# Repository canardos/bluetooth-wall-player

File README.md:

# Bluetooth Wall Audio Player

## A low power, wall mounted, Bluetooth audio player, clock, and environmental monitor

> [!Warning]
> This is personal project. It was built and works without issue for my purposes. It is made public here in case some part of it is useful to others, but **neither the hardware nor firmware have been rigorously tested**.

**Features:**

- Media/volume controls
- Song metadata display
- Time, temperature, pressure, humidity display on idle
- Ultra low power sleep with proximity sensing wakeup
- Differential analog and S/PDIF digital audio output

**This repo contains the firmware and PCB/enclosure design.**

**See [custom electronics projects at duk.io](https://www.duk.io/blog/electronics-projects/) for full project details.**

## Build

The project uses the [PlatformIO](https://platformio.org/) dependency management/build system. If you have PlatformIO installed, executing the `run` command in the root folder *should* 🙏 be all that is required for a successful build. The `platformio.ini` file contains the required configuration  and PlatformIO will download the required platform dependencies and toolchain.

**1. Clone repo and download submodules**

```shell
> git clone https://github.com/canardos/bluetooth-wall-player.git
> cd bluetooth-wall-player
> git submodule update --init
```

**2. Build firmware (PlatformIO must be installed)**

```shell
> pio run

```

**3. Upload to device**

Similarly, use `pio run --target upload` to upload the firmware to the device. You'll likely need to update the upload settings in `platformio.ini` to reflect your settings, or use your own upload tool.

```shell
> pio run --target upload

```

**4. [optional] Create project files for IDE**

If you want to view/edit the project in your favorite IDE, use PlatformIO to generate the appropriate setup/workspace files and import the project:

```shell
> pio project init --ide [atom|clion|codeblocks|eclipse|emacs|netbeans|qtcreator|sublimetext|vim|visualstudio|vscode]
```

See the [PlatformIO documentation](https://docs.platformio.org) for further details.

#### Using an alternate build system

**Platform dependencies**

If you wish to use a different build system, you will need:

| | |
|-|-|
| ST STM32 CMSIS headers | Peripheral/register definitions |
| CMSIS headers/source | CMSIS HAL functionality - SysTick_Config, NVIC_xxx etc.|
| CMSIS Cortex-M3 system source | `SystemInit()`/`SystemCoreClockUpdate()` implementation and `SystemCoreClock`|
| Startup source file | ASM file containing the startup code and vector table |
| Linker script | Tells the linker how to setup everything in flash/SRAM |

All of these are available in the [STM32 SDK](https://www.st.com/en/development-tools/stm32-software-development-tools.html) available from ST Micro.

**Compiling / linking**

`platformio.ini` lists the required compiler flags. Be sure to use `--specs=nano.specs` and `--specs=nosys.specs` when linking using your own tools.

#### Compiler

The project was built with `gcc-arm-none-eabi 9.2.1` It should work with any later GCC version and possibly with other compilers. The code contains some GCC flags and some C99 VLAs.

#### Target requirements

| | |
|-|-|
|MCU  | STM32F1xx |
|Flash| >42kb     |
|SRAM | >8kb      |

## Dependencies (firmware)

**CMSIS**

PlatformIO should automatically include/link the correct headers/sources from the STM32 SDK. Version 9.0.0 was used in production.

**Libpekin**

[Libpekin](https://github.com/canardos/libpekin) is a collection of shared MCU-related code resulting from this and other projects. It's included as a Git submodule in the `lib` folder. PlatformIO will include the `lib` subfolders automatically.

## Hardware

#### PCB

The PCB was designed with KiCad v.5, but the files have been upgraded to v.7 and are located in `/hardware/pcb`. Gerber output for the first revision is located in `/hardware/pcb/plots_rev_a`.

> [!Important]
> [Several fixes have been made to the design](https://www.duk.io/blog/electronics-projects/bt-player/bluetooth-audio-player-conclusion/#problems-and-screwups), which are implemented in the latest schematic/pcb files, but are not present in the revision A plot output.

See the [KiCad documentation](https://docs.kicad.org/) for information on installing and using KiCad.

**Custom symbols and footprints required by the board are included as a Git submodule at `/hardware/pcb/kicad-mycustom-lib`, and are included in the KiCad project as a project-specific library.**

#### Enclosure

The [enclosure design](http://www.duk.io/blog/electronics-projects/bt-player/bluetooth-audio-player-mechanical-design/#mechanical-design) includes a [laser-cut wooden facade](http://www.duk.io/blog/electronics-projects/bt-player/bluetooth-audio-player-mechanical-design/#laser-etched-wood-facade). The CAD files for the design are located in `/hardware/enclosure/laser_cut_facade`.

A Sketchup model I used to model the mechanical constraints of the design is included in `/hardware/enclosure`.

## Folder structure

```
BTWallPlayer
|
+--artwork           | SVG sources for animation
|  |
|  +--render         | bitmap output frames
|
+--hardware
|  |
|  +--pcb           | KiCad schematic and board design files
|  +--enclosure     | Enclosure Sketchup model and laser cutting
|                   | design files
|
+--lib
|  |
|  +--libpekin       | Libpekin platform independent code
|  +--libpekin_stm32 | Libpekin STM32 specific code
|
+--src
|  |
|  +--data           | Image and font data
|  +--devices        | Hardware device drivers
|
|--test              | No tests in use

```

## License

This software is available under the [MIT license](https://opensource.org/license/MIT).

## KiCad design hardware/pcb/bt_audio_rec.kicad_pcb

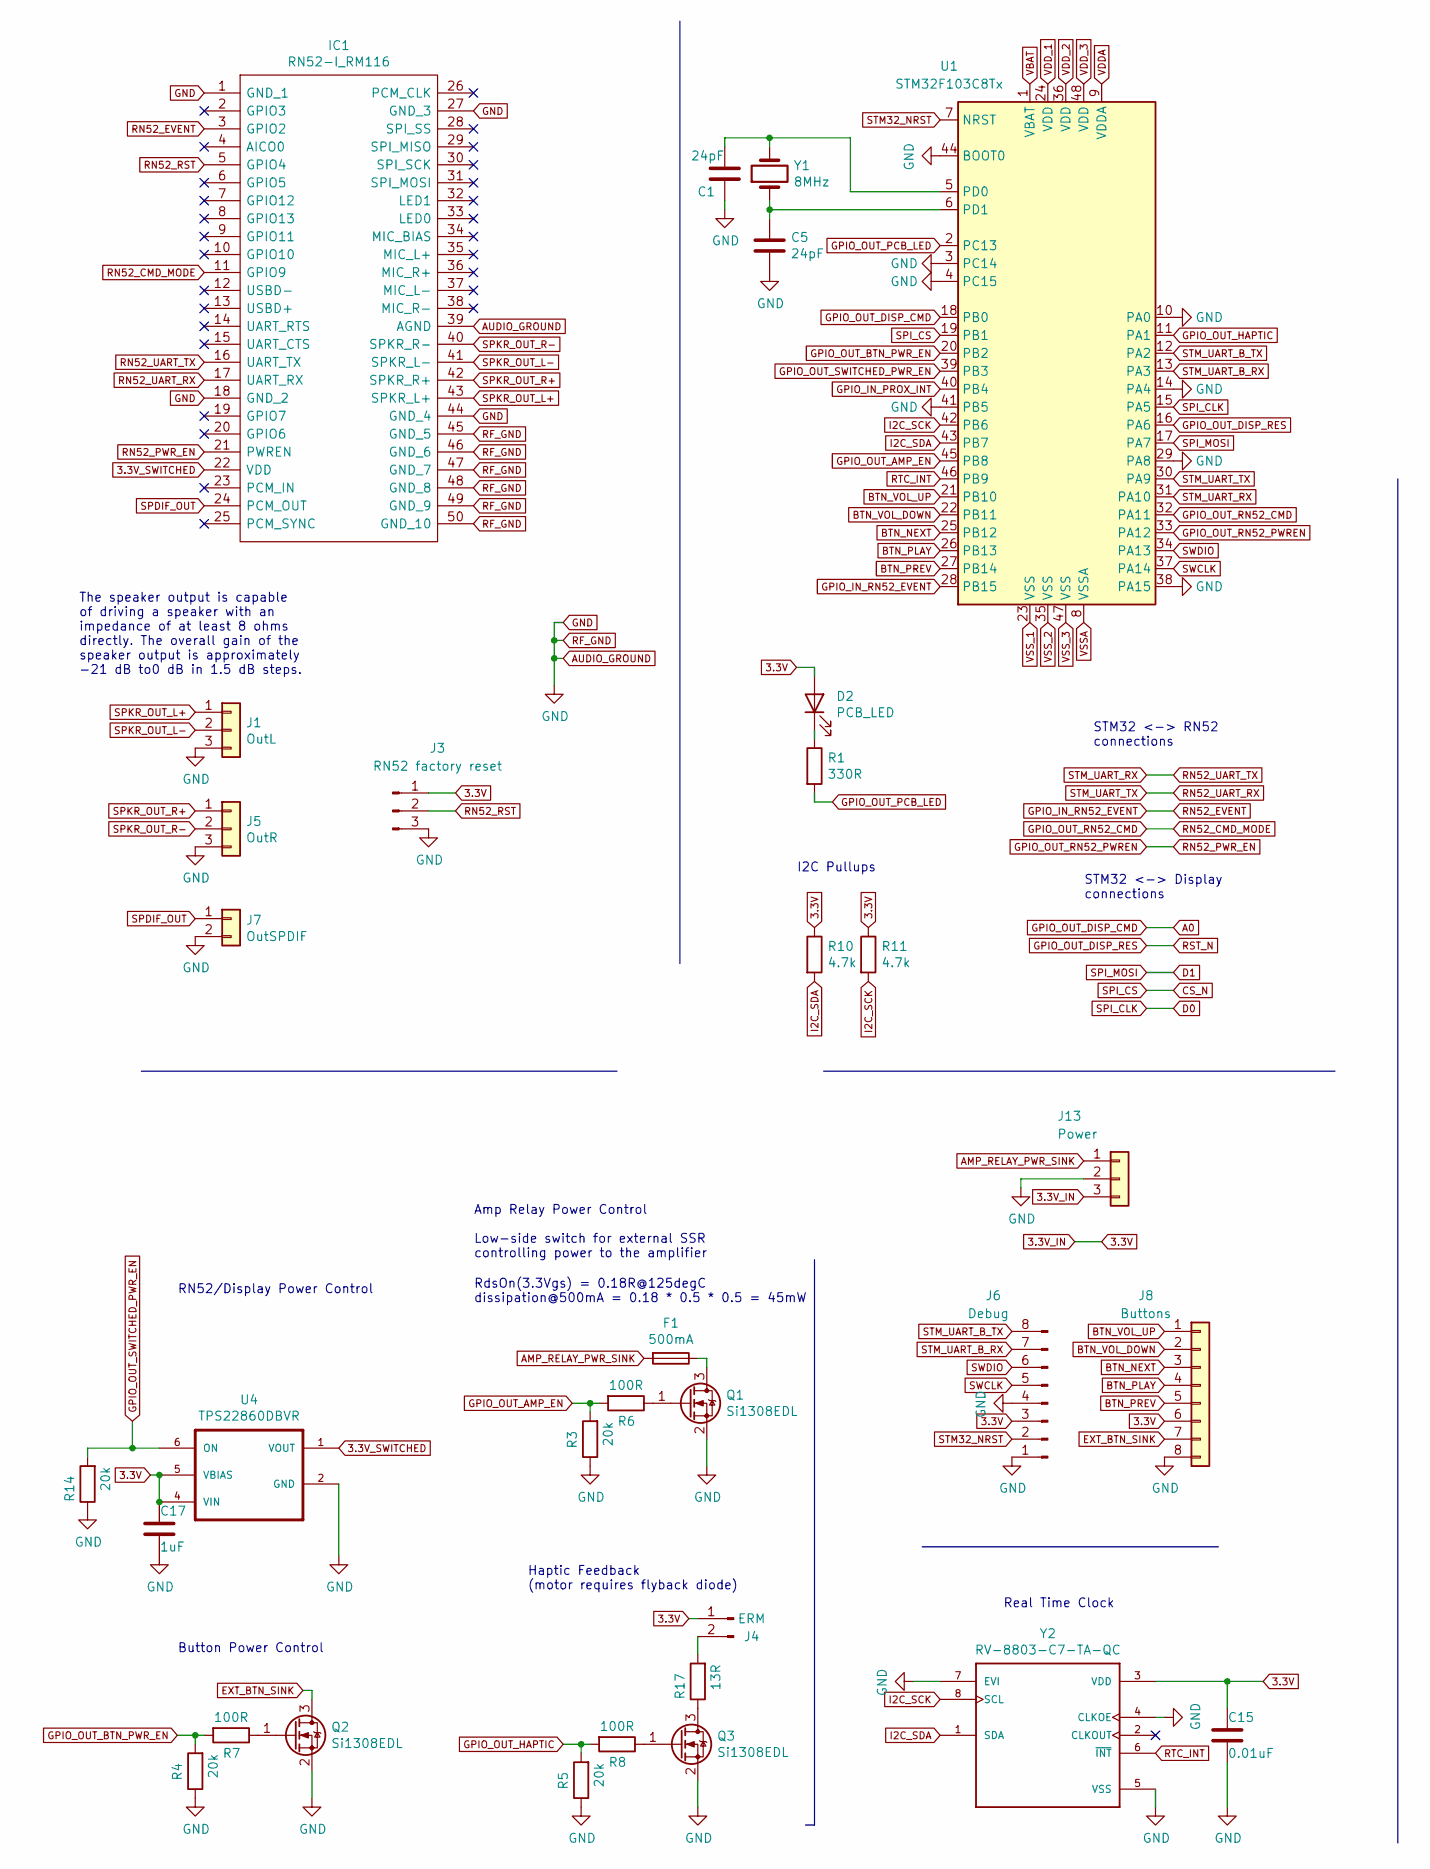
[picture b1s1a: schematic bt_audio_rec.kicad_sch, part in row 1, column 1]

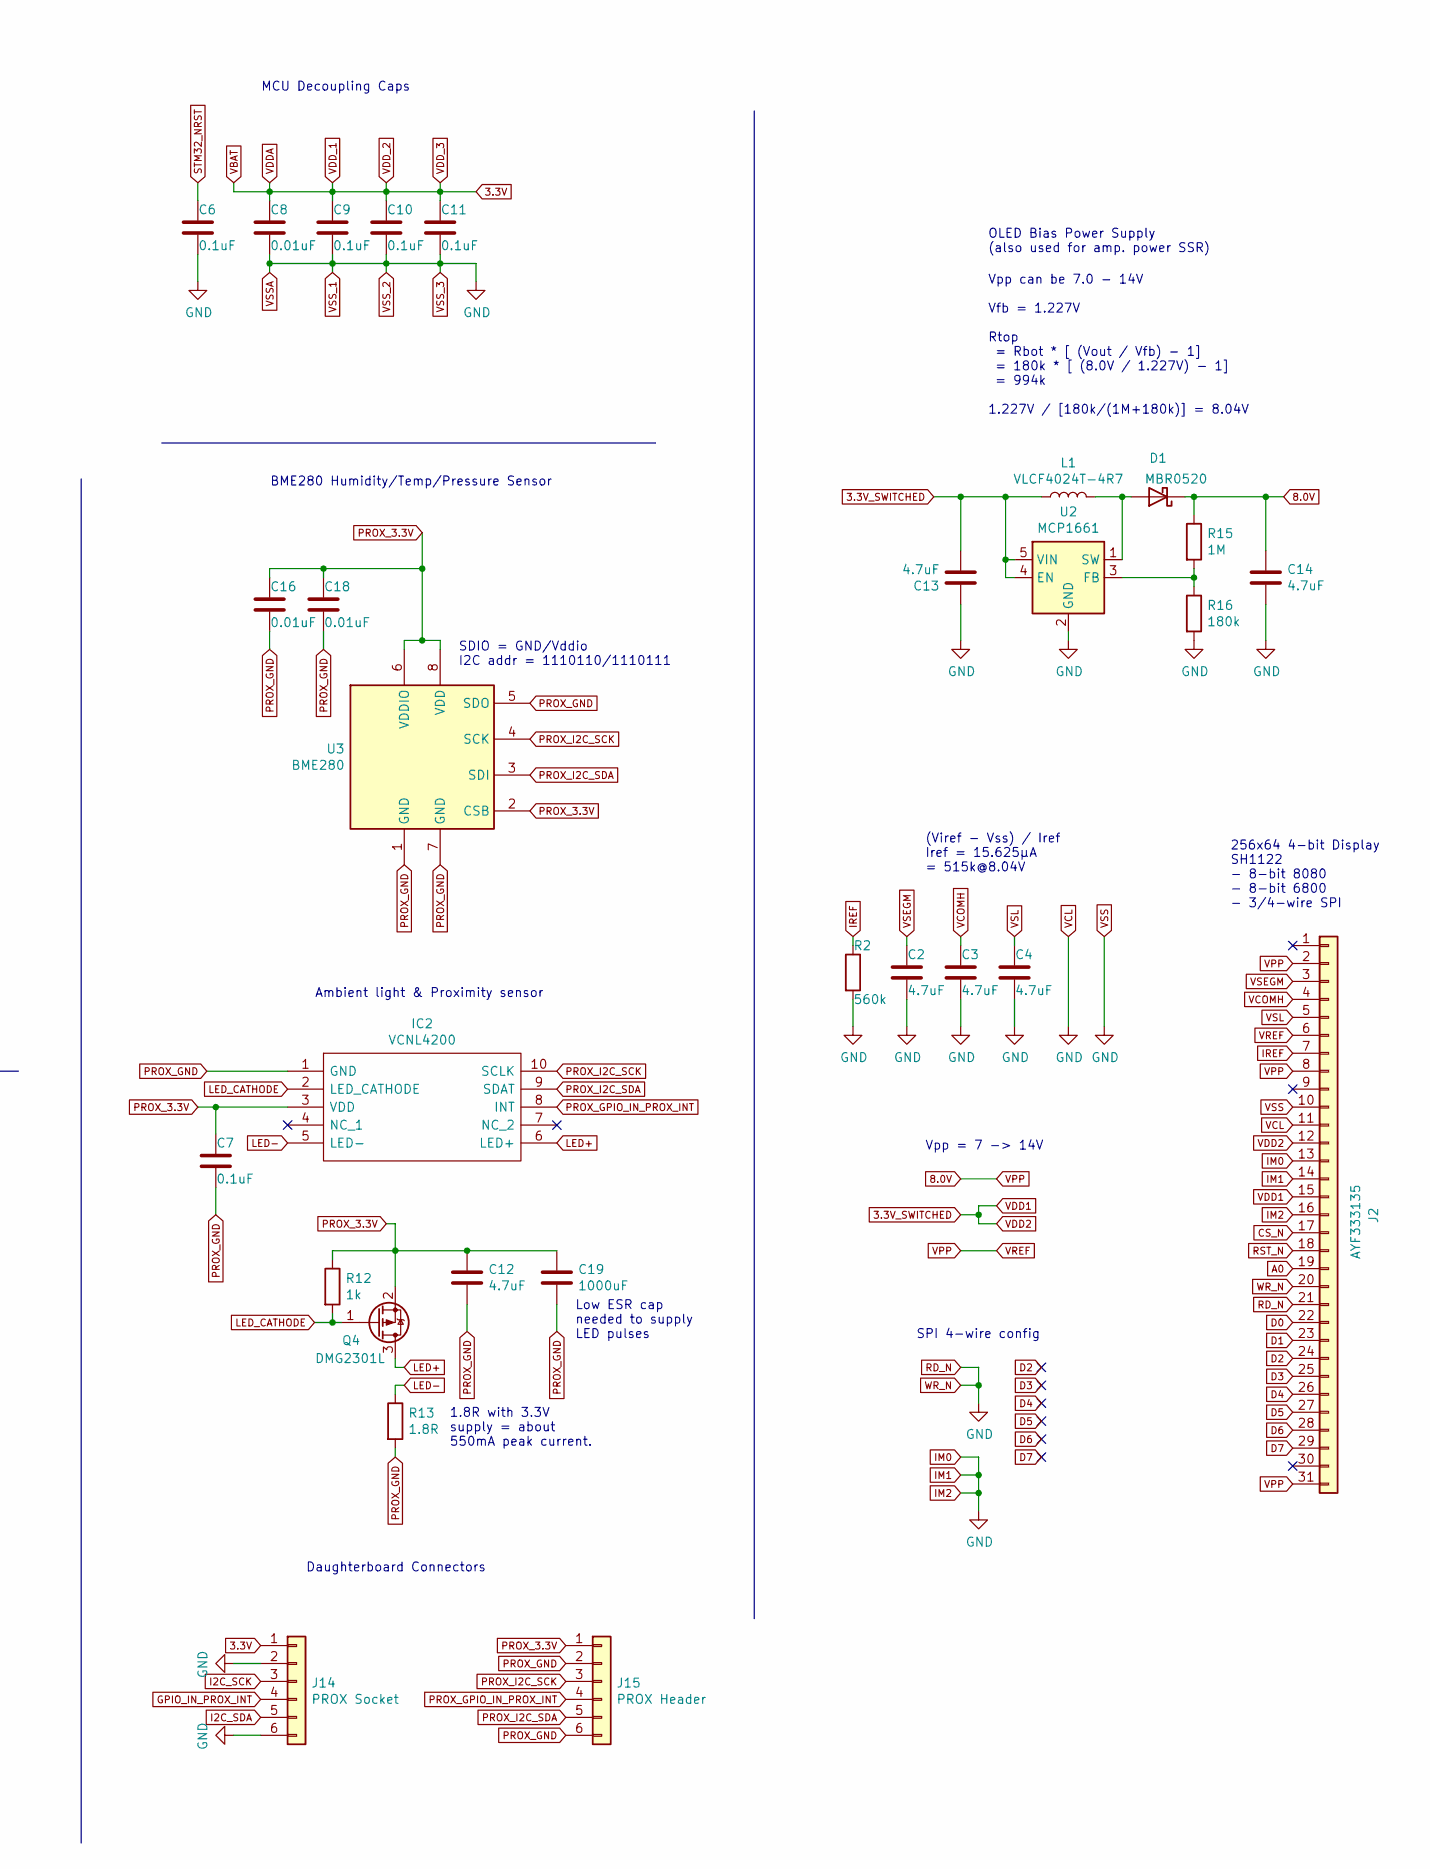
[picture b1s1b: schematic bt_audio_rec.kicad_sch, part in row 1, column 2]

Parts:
C1, C5: 24pF; C_0402_1005Metric
C2, C3, C4, C12, C13, C14: 4.7uF; C_0603_1608Metric
C6, C7, C9, C10, C11: 0.1uF; C_0402_1005Metric
C8, C15, C16, C18: 0.01uF; C_0402_1005Metric
C17: 1uF; C_0805_2012Metric
C19: 1000uF; C_Radial_D6.3mm_H7.0mm_P2.50mm
D1: MBR0520; D_SOD-123
D2: PCB_LED; D_0603_1608Metric
F1: 500mA; R_Axial_DIN0207_L6.3mm_D2.5mm_P10.16mm_Horizontal
IC1: RN52-I_RM116; Bluetooth_module_Microchip_RN52; Manufacturer_Part_Number RN52-I/RM116; Mouser Part Number 579-RN52-I/RM116
IC2: VCNL4200; Proximity_Sensor_Vishay_VCNL4200; Manufacturer_Part_Number VCNL4200; Mouser Part Number 78-VCNL4200
J1: OutL; JST_PH_B3B-PH-K_1x03_P2.00mm_Vertical
J2: AYF333135; FPC_Socket_0.3_31_Panasonic_AYF333135
J3: RN52 factory reset; PinHeader_1x03_P2.54mm_Horizontal
J4: ERM; PinHeader_1x02_P2.54mm_Horizontal
J5: OutR; JST_PH_B3B-PH-K_1x03_P2.00mm_Vertical
J6: Debug; PinSocket_2x04_P2.54mm_Vertical
J7: OutSPDIF; JST_PH_B2B-PH-K_1x02_P2.00mm_Vertical
J8: Buttons; PinHeader_1x08_P2.54mm_Horizontal
J13: Power; Molex_KK-254_AE-6410-03A_1x03_P2.54mm_Vertical
J14: PROX Socket; PinSocket_2x03_P2.54mm_Vertical
J15: PROX Header; PinHeader_2x03_P2.54mm_Vertical
L1: VLCF4024T-4R7; Inductor_L_TDK_VLCF4024
Q1, Q2, Q3: Si1308EDL; SOT-323_SC-70
Q4: DMG2301L; SOT-23
R1: 330R; R_0603_1608Metric
R2: 560k; R_0603_1608Metric
R3, R4, R5, R14: 20k; R_0603_1608Metric
R6, R7, R8: 100R; R_0603_1608Metric
R10, R11: 4.7k; R_0603_1608Metric
R12: 1k; R_0603_1608Metric
R13: 1.8R; R_0603_1608Metric
R15: 1M; R_0603_1608Metric
R16: 180k; R_0603_1608Metric
R17: 13R; R_0603_1608Metric
U1: STM32F103C8Tx; LQFP-48_7x7mm_P0.5mm
U2: MCP1661; SOT-23-5
U3: BME280; Bosch_LGA-8_2.5x2.5mm_P0.65mm_ClockwisePinNumbering
U4: TPS22860DBVR; SOT-23-6
Y1: 8MHz; Crystal_SMD_HC49-SD
Y2: RV-8803-C7-TA-QC; RTC_Microcrystal_RV-8803-C7-TA-QC

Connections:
3.3V: C8.1, C9.1, C10.1, C11.1, C15.1, C17.1, D2.2 (A), J3.1, J4.1, J6.3, J8.6, J13.3, J14.1, R10.1, R11.1, U1.1 (VBAT), U1.9 (VDDA), U1.24 (VDD), U1.36 (VDD), U1.48 (VDD), U4.4 (VIN), U4.5 (VBIAS), Y2.3 (VDD)
3.3V_SWITCHED: C13.2, IC1.22 (VDD), J2.12, J2.15, L1.1, U2.4 (EN), U2.5 (VIN), U4.1 (VOUT)
8.0V: C14.1, D1.1 (K), J2.2, J2.6, J2.8, J2.31, R15.1
A0: J2.19, U1.18 (PB0)
AMP_RELAY_PWR_SINK: F1.2, J13.1
AUDIO_GROUND: C1.1, C2.2, C3.2, C4.2, C5.2, C6.2, C8.2, C9.2, C10.2, C11.2, C13.1, C14.2, C15.2, C17.2, IC1.1 (GND_1), IC1.18 (GND_2), IC1.27 (GND_3), IC1.39 (AGND), IC1.44 (GND_4), IC1.45 (GND_5), IC1.46 (GND_6), IC1.47 (GND_7), IC1.48 (GND_8), IC1.49 (GND_9), IC1.50 (GND_10), J1.3, J2.10, J2.11, J2.13, J2.14, J2.16, J2.20, J2.21, J3.3, J5.3, J6.1, J6.4, J7.2, J8.8, J13.2, J14.2, J14.6, Q1.2 (S), Q2.2 (S), Q3.2 (S), R2.2, R3.1, R4.1, R5.1, R14.1, R16.2, U1.3 (PC14), U1.4 (PC15), U1.8 (VSSA), U1.10 (PA0), U1.14 (PA4), U1.23 (VSS), U1.29 (PA8), U1.35 (VSS), U1.38 (PA15), U1.41 (PB5), U1.44 (BOOT0), U1.47 (VSS), U2.2 (GND), U4.2 (GND), Y2.4 (CLKOE), Y2.5 (VSS), Y2.7 (EVI)
BTN_NEXT: J8.3, U1.25 (PB12)
BTN_PLAY: J8.4, U1.26 (PB13)
BTN_PREV: J8.5, U1.27 (PB14)
BTN_VOL_DOWN: J8.2, U1.22 (PB11)
BTN_VOL_UP: J8.1, U1.21 (PB10)
CS_N: J2.17, U1.19 (PB1)
D0: J2.22, U1.15 (PA5)
D1: J2.23, U1.17 (PA7)
D2: J2.24
D3: J2.25
D4: J2.26
D5: J2.27
D6: J2.28
D7: J2.29
EXT_BTN_SINK: J8.7, Q2.3 (D)
GPIO_IN_PROX_INT: J14.4, U1.40 (PB4)
GPIO_IN_RN52_EVENT: IC1.3 (GPIO2), U1.28 (PB15)
GPIO_OUT_AMP_EN: R3.2, R6.2, U1.45 (PB8)
GPIO_OUT_BTN_PWR_EN: R4.2, R7.2, U1.20 (PB2)
GPIO_OUT_DISP_RES: J2.18, U1.16 (PA6)
GPIO_OUT_HAPTIC: R5.2, R8.2, U1.11 (PA1)
GPIO_OUT_PCB_LED: R1.2, U1.2 (PC13)
GPIO_OUT_RN52_CMD: IC1.11 (GPIO9), U1.32 (PA11)
GPIO_OUT_RN52_PWREN: IC1.21 (PWREN), U1.33 (PA12)
GPIO_OUT_SWITCHED_PWR_EN: R14.2, U1.39 (PB3), U4.6 (ON)
I2C_SCK: J14.3, R11.2, U1.42 (PB6), Y2.8 (SCL)
I2C_SDA: J14.5, R10.2, U1.43 (PB7), Y2.1 (SDA)
IREF: J2.7, R2.1
LED+: IC2.6 (LED+), Q4.3 (D)
LED-: IC2.5 (LED-), R13.1
LED_CATHODE: IC2.2 (LED_CATHODE), Q4.1 (G), R12.2
unnamed: C1.2, U1.5 (PD0), Y1.2
unnamed: C5.1, U1.6 (PD1), Y1.1
unnamed: D1.2 (A), L1.2, U2.1 (SW)
unnamed: D2.1 (K), R1.1
unnamed: F1.1, Q1.3 (D)
unnamed: J4.2, R17.2
unnamed: Q1.1 (G), R6.1
unnamed: Q2.1 (G), R7.1
unnamed: Q3.1 (G), R8.1
unnamed: Q3.3 (D), R17.1
unnamed: R15.2, R16.1, U2.3 (FB)
PROX_3.3V: C7.1, C12.1, C16.1, C18.1, C19.1, IC2.3 (VDD), J15.1, Q4.2 (S), R12.1, U3.2 (CSB), U3.6 (VDDIO), U3.8 (VDD)
PROX_GND: C7.2, C12.2, C16.2, C18.2, C19.2, IC2.1 (GND), J15.2, J15.6, R13.2, U3.1 (GND), U3.5 (SDO), U3.7 (GND)
PROX_GPIO_IN_PROX_INT: IC2.8 (INT), J15.4
PROX_I2C_SCK: IC2.10 (SCLK), J15.3, U3.4 (SCK)
PROX_I2C_SDA: IC2.9 (SDAT), J15.5, U3.3 (SDI)
RN52_RST: IC1.5 (GPIO4), J3.2
RN52_UART_RX: IC1.17 (UART_RX), U1.30 (PA9)
RN52_UART_TX: IC1.16 (UART_TX), U1.31 (PA10)
RTC_INT: U1.46 (PB9), Y2.6 (~INT)
SPDIF_OUT: IC1.24 (PCM_OUT), J7.1
SPKR_OUT_L+: IC1.43 (SPKR_L+), J1.1
SPKR_OUT_L-: IC1.41 (SPKR_L-), J1.2
SPKR_OUT_R+: IC1.42 (SPKR_R+), J5.1
SPKR_OUT_R-: IC1.40 (SPKR_R-), J5.2
STM32_NRST: C6.1, J6.2, U1.7 (NRST)
STM_UART_B_RX: J6.7, U1.13 (PA3)
STM_UART_B_TX: J6.8, U1.12 (PA2)
SWCLK: J6.5, U1.37 (PA14)
SWDIO: J6.6, U1.34 (PA13)
VCOMH: C3.1, J2.4
VSEGM: C2.1, J2.3
VSL: C4.1, J2.5

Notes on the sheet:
Haptic Feedback (motor requires flyback diode)
Daughterboard Connectors
I2C Pullups
Amp Relay Power Control Low-side switch for external SSR controlling power to the amplifier
Vpp can be 7.0 - 14V Vfb = 1.227V Rtop = Rbot * [ (Vout / Vfb) - 1] = 180k * [ (8.0V / 1.227V) - 1] = 994k 1.227V / [180k/(1M+180k)] = 8.04V
BME280 Humidity/Temp/Pressure Sensor
SDIO = GND/Vddio I2C addr = 1110110/1110111
(Viref - Vss) / Iref Iref = 15.625μA = 515k@8.04V
The speaker output is capable of driving a speaker with an impedance of at least 8 ohms directly. The overall gain of the speaker output is approximately -21 dB to0 dB in 1.5 dB steps.
Low ESR cap needed to supply LED pulses
Button Power Control
RdsOn(3.3Vgs) = 0.18R@125degC dissipation@500mA = 0.18 * 0.5 * 0.5 = 45mW
1.8R with 3.3V supply = about 550mA peak current.
Vpp = 7 -> 14V
STM32 <-> Display connections
Ambient light & Proximity sensor
RN52/Display Power Control
OLED Bias Power Supply (also used for amp. power SSR)
Real Time Clock
STM32 <-> RN52 connections
256x64 4-bit Display SH1122 - 8-bit 8080 - 8-bit 6800 - 3/4-wire SPI
MCU Decoupling Caps
SPI 4-wire config

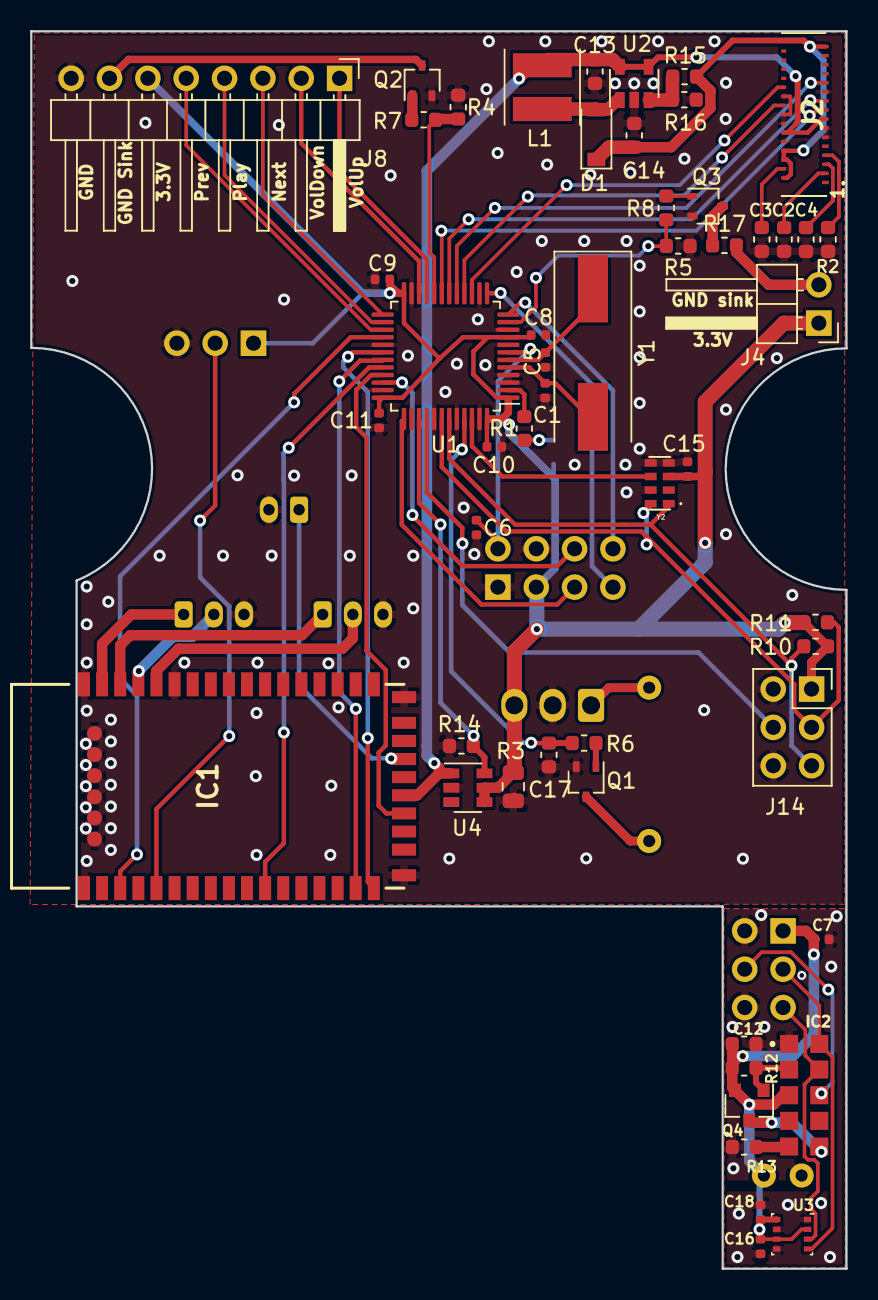
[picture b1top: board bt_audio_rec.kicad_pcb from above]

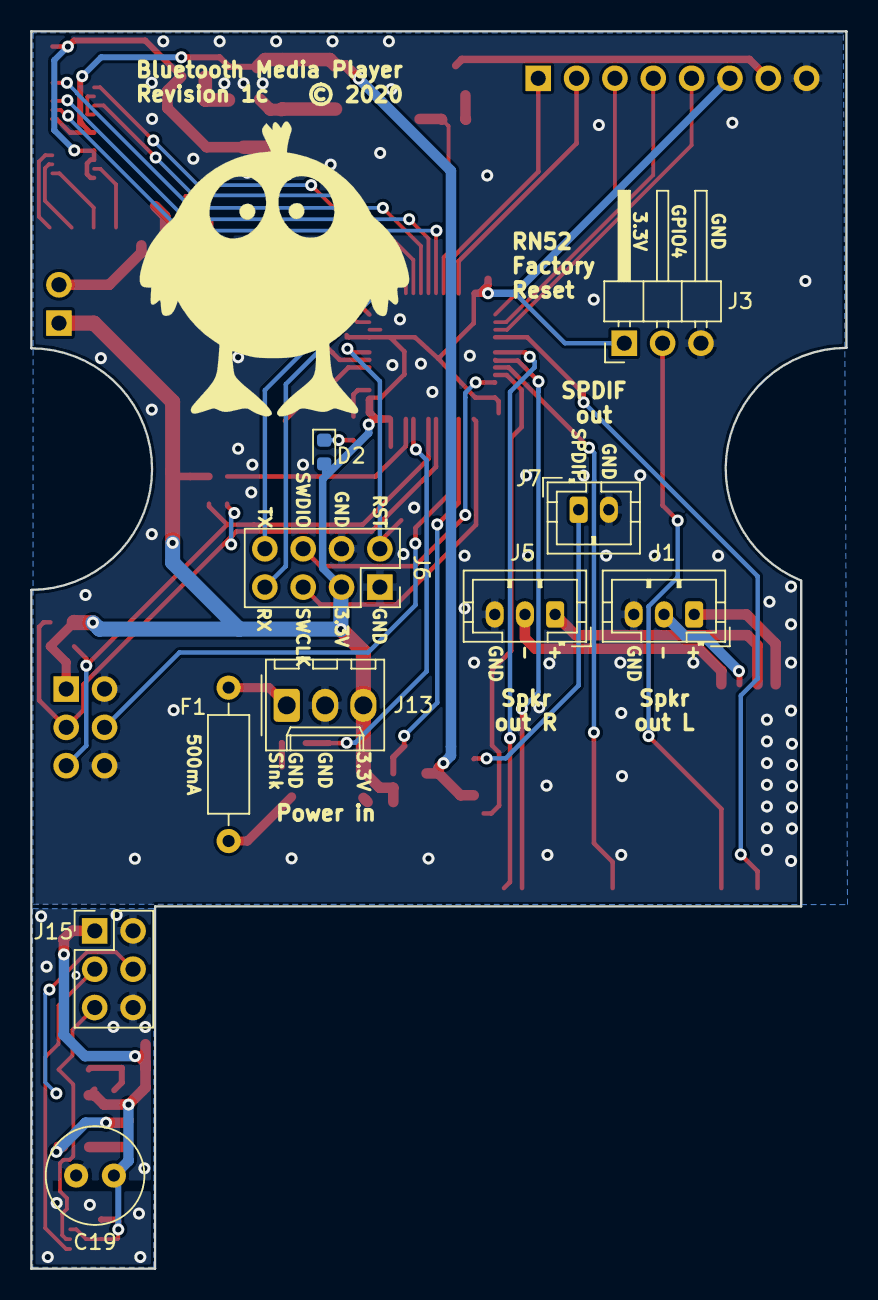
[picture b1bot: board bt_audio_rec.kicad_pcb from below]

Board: 2 copper layers, 54.0 x 82.0 mm, 62 parts (10 on the bottom side), 64 nets.

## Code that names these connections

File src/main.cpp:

#include "libpekin.h"
#include "string_util.h"
#include "libpekin_stm32_hal.h"
#include "clock_stm32f1xx.h"

#include <bt_module.h>
#include <error_handler.h>
#include <event_queue.h>
#include <player_state_machine.h>

#include <devices/peripherals.h>
#include <devices/rn52.h>
#include "devices/oled.h"
#include "devices/sensors.h"
#include "devices/rtc.h"

/*
3.3V / GND / sink
blue /white/brown, left to right front of faceplate
brown/black/blue cable
*/

using namespace Libp;
using namespace LibpStm32;

static BtModule bt_module_(getRn52());
static Display display(getOled());
static PwrControl pwr_ctrl;
static EventQueue queue_;
static PlayerStateMachine player(queue_, bt_module_, display, pwr_ctrl);

void initSysClock()
{
    Clk::setSysClk(Clk::SysClkSrc::ext_high_speed_osc, 2, Clk::PllSrc::hse, 2);
    // 24 MHz
    Clk::setSysClk(Clk::SysClkSrc::pll, 2, Clk::PllSrc::hse, 3);
    // APB1 can't exceed 36 MHz
    Clk::setPeripheralClk(Clk::ApbPrescaler::div1, Clk::ApbPrescaler::div1);
}

void initSensors()
{
    if (!initTempSensor()) {
        getErrHndlr().halt(ErrorCode::module_init_fail, "BME280 init failed");
    }
    if (!initRtc()) {
        getErrHndlr().halt(ErrorCode::module_init_fail, "RTC init failed");
    }

    display.drawText(Display::TextPos::fullscreen, "Calibrating proximity", "in 3");
    delayMs(1000);
    display.drawText(Display::TextPos::fullscreen, "Calibrating proximity", "in 2");
    delayMs(1000);
    display.drawText(Display::TextPos::fullscreen, "Calibrating proximity", "in 1");
    delayMs(1000);

    uint16_t prox_count = initProxSensor();
    if (prox_count == 0) {
        getErrHndlr().halt(ErrorCode::module_init_fail, "Prox init failed");
    }

    constexpr uint8_t max_len = strlen("Done ()") + Libp::maxStrLen<uint16_t>();
    char buf[max_len];
    snprintf(buf, max_len, "Done (%d)", prox_count);
    display.drawText(Display::TextPos::fullscreen, buf, "Initializing Bluetooth...");

    TimeData time_data = {0};
    time_data.year = 20;
    time_data.month = 1;
    time_data.day_of_month = 1;
    setTime(time_data);
}

//#define TEST_PROX_MODE

#ifdef TEST_PROX_MODE
void drawProx()
{
    char buf[50];
    while (true) {
        uint16_t count = getProxCount();
        snprintf(buf, 50, "Count: %d", count);
        display.drawText(Display::TextPos::fullscreen, buf, "");
        delayMs(300);
    }
}
#endif

void initPeripherals()
{
    initGpio();  // enable GPIO clocks before peripherals init
    initSerial();
    initSpi();
    initI2c();
    initTimers();
    initErrHndlr();
}

int main(void)
{
    initSysClock();
    libpekinInitTimers();
    initPeripherals();
    pwr_ctrl.setState(PwrControl::PwrState::clock); // needs errHndlr
    oledInit();                                     // needs SPI and timers
    initSensors();                                  // needs I2C, timers, and display
#ifdef TEST_PROX_MODE
    drawProx();
#endif
    initRn52();
    if (!bt_module_.init()) {
        getErrHndlr().halt(ErrorCode::module_init_fail, "BT init failed");
    }
    enableExtIrqs();
    clearProxInterrupt();
    player.run();
}

#ifdef __cplusplus
extern "C" {
#endif

/// Triggered by RN52 event on GPIO2 and button presses
__attribute__ ((interrupt("IRQ")))
void EXTI15_10_IRQHandler(void)
{
    disableExtIrqs();
    getErrHndlr().report("\r\nEXTI15_10_IRQ\r\n");

    // --- RN52 event ---

    if (Pins::rn52_gpio2.irqIsPending()) {
        queue_.postEvent(EventType::rn52_gpio2);
        Pins::rn52_gpio2.clearPendingIrqBit();
    }

    // --- Button events ---

    if (Pins::btn_play.irqIsPending()) {
        bool pressed = Pins::btn_play.read();
        getErrHndlr().report("Play: %d\r\n", (int)pressed);
        queue_.postEvent(pressed ? EventType::btn_play : EventType::btn_play_release);
        Pins::btn_play.clearPendingIrqBit();
    }
    if (Pins::btn_vol_up.irqIsPending()) {
        queue_.postEvent(EventType::btn_vol_up);
        Pins::btn_vol_up.clearPendingIrqBit();
    }
    if (Pins::btn_vol_dn.irqIsPending()) {
        queue_.postEvent(EventType::btn_vol_dn);
        Pins::btn_vol_dn.clearPendingIrqBit();
    }
    if (Pins::btn_next.irqIsPending()) {
        queue_.postEvent(EventType::btn_next);
        Pins::btn_next.clearPendingIrqBit();
    }
    if (Pins::btn_prev.irqIsPending()) {
        queue_.postEvent(EventType::btn_prev);
        Pins::btn_prev.clearPendingIrqBit();
    }
    Pins::btn_prev.clearPendingIrqLine();
    //__DSB();
    enableExtIrqs();
}

/// Triggered by RTC minute tick
__attribute__ ((interrupt("IRQ")))
void EXTI9_5_IRQHandler(void)
{
    getErrHndlr().report("\r\nEXTI9_5_IRQ\r\n");
    if (Pins::rtc_int.irqIsPending()) {
        queue_.postEvent(EventType::clock_tick);
        Pins::rtc_int.clearPendingIrqBit();
    }
    Pins::rtc_int.clearPendingIrqLine();
    __DSB();
}

/// Triggered by proximity sensor
__attribute__ ((interrupt("IRQ")))
void EXTI4_IRQHandler(void)
{
    getErrHndlr().report("\r\nEXTI4_IRQ\r\n");
    if (Pins::proximity_int.irqIsPending()) {
        queue_.postEvent(EventType::proximity_trigger);
        Pins::proximity_int.clearPendingIrqBit();
    }
    Pins::proximity_int.clearPendingIrqLine();
    __DSB();
}

#ifdef __cplusplus
}
#endif

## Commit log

2020-03-12 Initial commit - PCB hardware production ver.A
2020-09-09 Update proximity cap value, upate PCB notes.
2020-09-22 Fix GPIO4 tied low and backwards MOSFET error
2020-09-23 Update connector label
2020-09-23 Rename plot output folder
2020-09-24 Connect unused pins to ground
2020-09-25 Add duk.io logo
2020-09-26 Change LED resistor
2020-09-29 Add FPC pin number label
2020-10-14 Add decoupling cap to proximity LED
    See https://www.duk.io/blog/electronics-projects/bt-player/bluetooth-audio-player-firmware
2020-11-19 Add flyback label
2024-03-29 Migrate to KiCad 7
    Update schematic/pcb and rescue symbols as required
    Move custom library to a project specific submodule
    Fix missing duk.io logo
    Update gitignore
    Remove old files
2024-04-01 Add project firmware
2024-04-01 Add hardware enclosure files
2024-04-01 Update libpekin library to correct commit

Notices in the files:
hardware/pcb/bt_audio_rec.kicad_pcb:
© 2020
